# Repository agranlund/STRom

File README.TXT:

----------------------------------------------------------------------------
ROM board for Atari STM
(c)2020, Anders Granlund
----------------------------------------------------------------------------
Tested on a C070243 Rev.I motherboard, your mileage may vary.
----------------------------------------------------------------------------

This board does not perform TOS2.x decoding but it has provisions to hook
it up to an external decoder.

pin CEO is the original chip select output
pin CEI is chip select input from external decoder

Bridge the CEO/CEI pins if you're not using an external TOS decoder.

----------------------------------------------------------------------------
TOS select header
----------------------------------------------------------------------------
The leftmost pin header can be used to select TOS when using EEPROMs big
enough to fit multiple TOSs on them.

Upper two pins controls A18 and the lower two controls A19.
Jumper to pull the signal low.

For example:
39SF010 fits one TOS (A18+A19 are ignored)
39SF020 fits two TOS's (A18 is used to select, A19 is ignored)
39SF040 fits four TOS's (both A18 and A19 are used to select)

----------------------------------------------------------------------------
ROM size mode:
----------------------------------------------------------------------------
If your motherboard has the 256K/1M rom size jumpers and has already been
adjusted to work in 1M mode then you need only to bridge the three
solder jumpers on the rom board to the 1M position.

If the motherboard is in 256K mode, or if it lacks rom jumpers,
then you need to do the following:
- Bridge the three solder jumpers to the 256K position.
- Fit the 74LS11
- Fit the 100nF capacitor next to the 74LS11
- Solder wires from A16+A17 from the CPU to the A16+A17 headers
  on the rom board.

----------------------------------------------------------------------------
Realtime clock:
----------------------------------------------------------------------------
It takes a Dallas DS1315 chip and drivers can be found here:
https://github.com/agranlund/rtc

If you don't fit the DS1315 you need to bridge the "disable"
solder jumper.

----------------------------------------------------------------------------
BOM:
----------------------------------------------------------------------------
- Pin headers and sockets
- R1+R2: pullup resistors. The value is not terribly important, I used 3K3's

- Dallas DS1315 realtime clock
- 32.768Khz occilator for DS1315
- C1: 100nf capacitor for DS1315
- Battery holder for DS1315. I am using this one:
https://www.electrokit.com/en/product/battery-holder-cr2016-2025-2032-plastic/

- 74LS11N for motherboards in 256K mode
- C2: 100nf capacitor 74LS11N

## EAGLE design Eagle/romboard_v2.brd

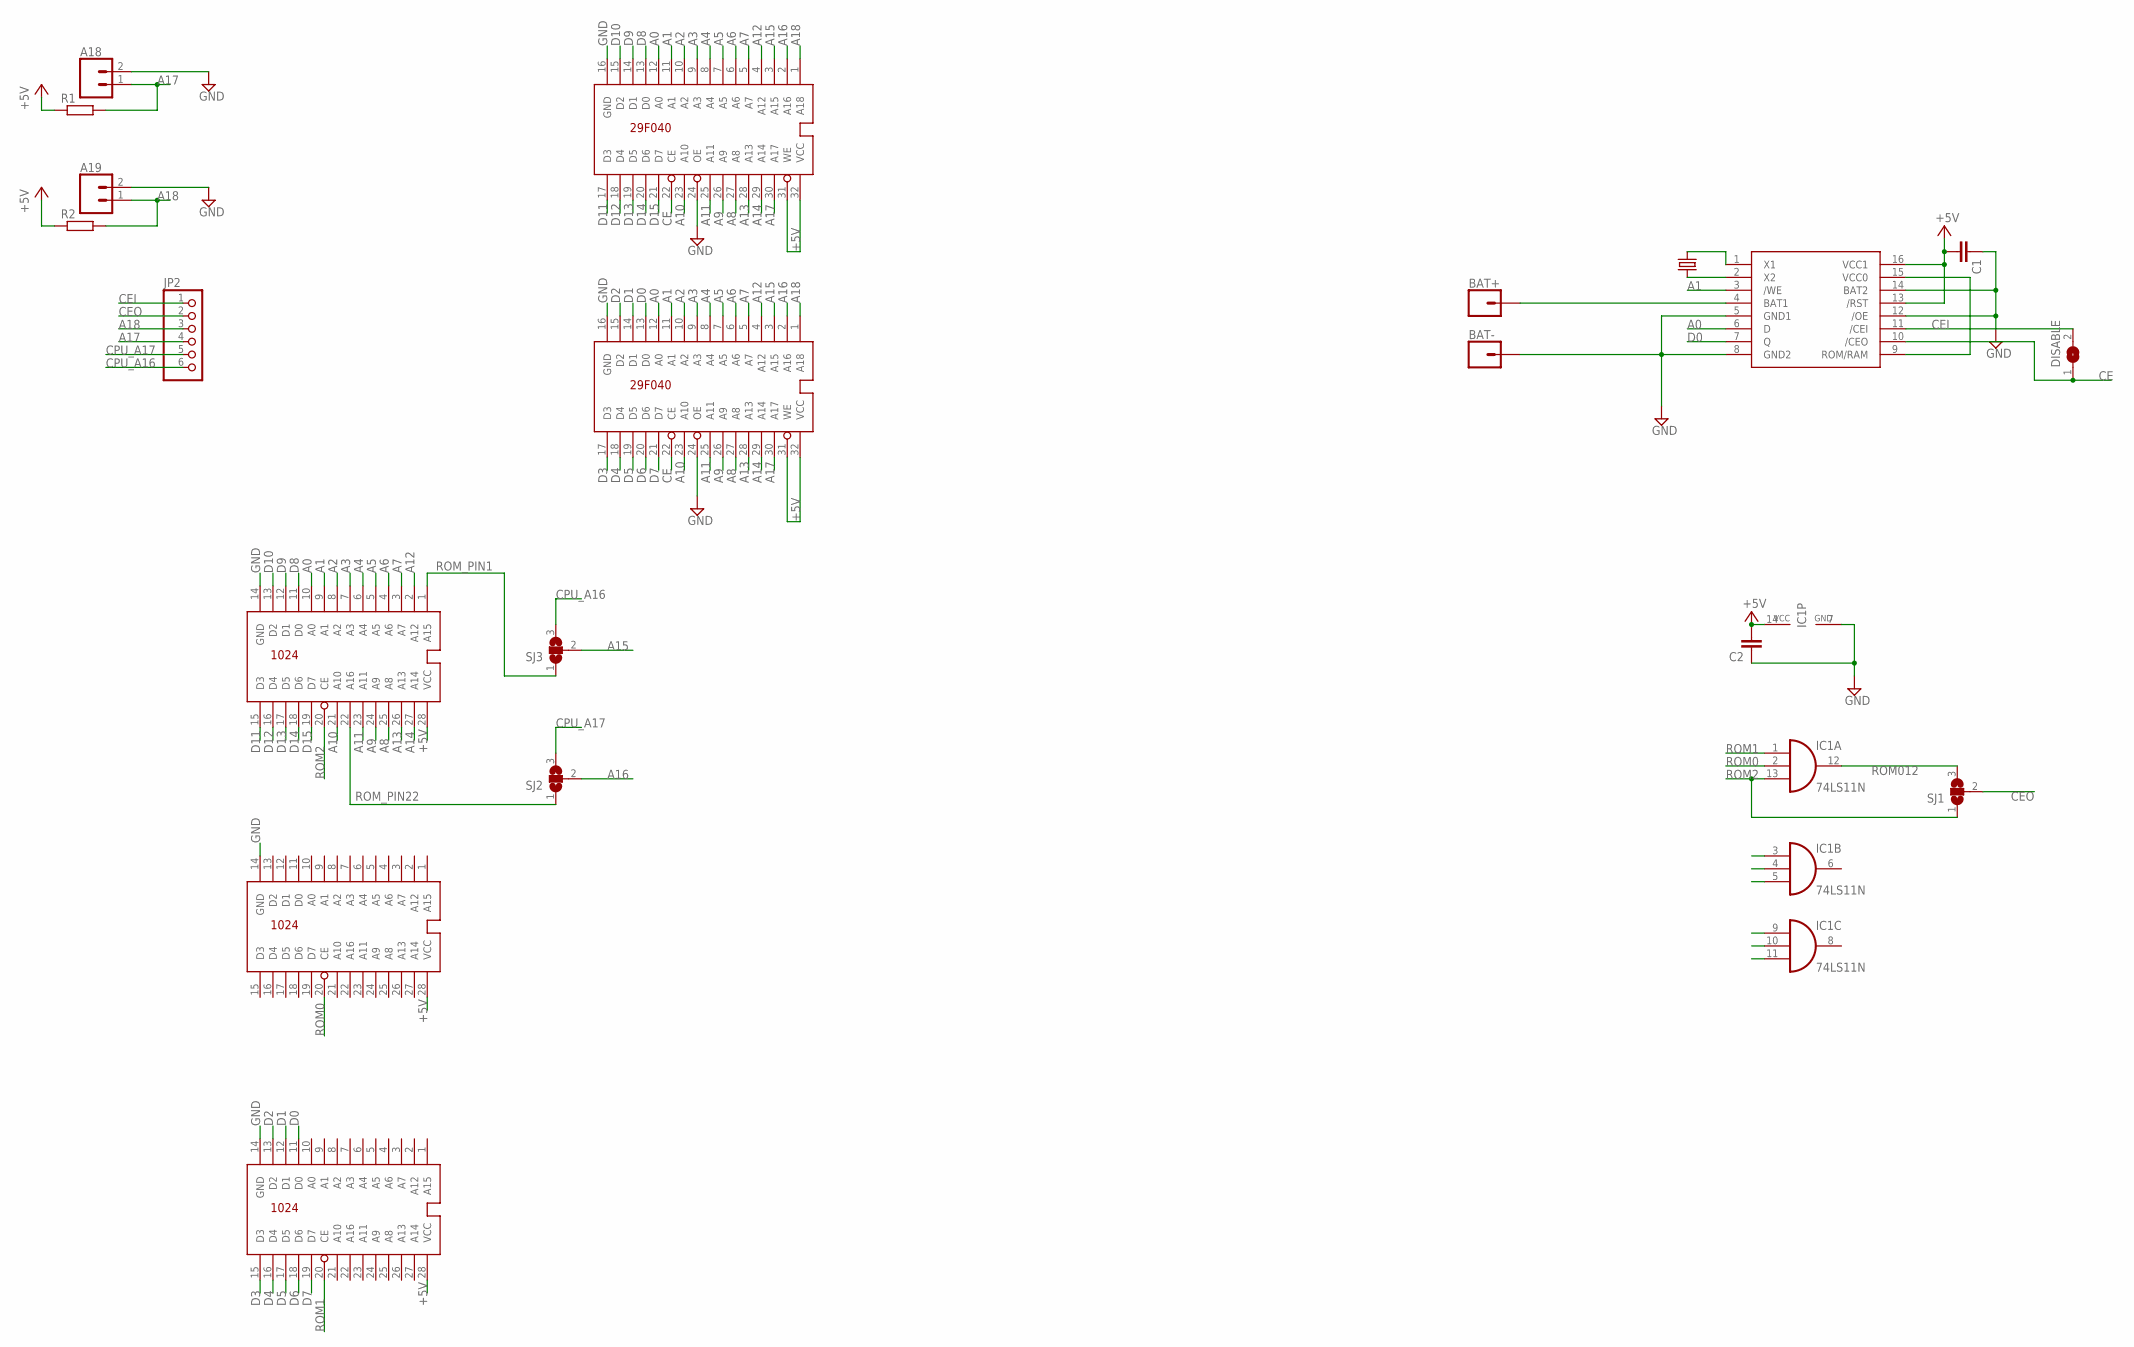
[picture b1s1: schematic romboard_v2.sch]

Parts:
32.768KHZ: CRYSTALTC38H; TC38H
A18, A19: CONN_02; 1X02
BAT+: CONN_01; 1X01
BAT-: CONN_01; 1X01
C1, C2: C-EU050-025X075; C050-025X075
DISABLE: SJ
HI0_SOCKET: ROM1024; ROM28PIN
IC1: 74LS11N; DIL14
JP2: PINHD-1X6/90; 1X06/90
LO2_SOCKET, LO2_SOCKET1: ROM1024; ROM28PIN
R1, R2: R-EU_0207/12; 0207/12
SJ1, SJ2, SJ3: SJ2W; SJ_2
U$1, U$2: AM29F040
U$4: DS1315; DIL16

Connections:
+5V: C1.2, C2.2, HI0_SOCKET.28 (VCC), IC1.14 (VCC), LO2_SOCKET.28 (VCC), LO2_SOCKET1.28 (VCC), R1.1, R2.1, U$1.31 (WE), U$1.32 (VCC), U$2.31 (WE), U$2.32 (VCC), U$4.13 (/RST), U$4.16 (VCC1)
A0: HI0_SOCKET.10 (A0), U$1.12 (A0), U$2.12 (A0), U$4.6 (D)
A1: HI0_SOCKET.9 (A1), U$1.11 (A1), U$2.11 (A1), U$4.3 (/WE)
A2: HI0_SOCKET.8 (A2), U$1.10 (A2), U$2.10 (A2)
A3: HI0_SOCKET.7 (A3), U$1.9 (A3), U$2.9 (A3)
A4: HI0_SOCKET.6 (A4), U$1.8 (A4), U$2.8 (A4)
A5: HI0_SOCKET.5 (A5), U$1.7 (A5), U$2.7 (A5)
A6: HI0_SOCKET.4 (A6), U$1.6 (A6), U$2.6 (A6)
A7: HI0_SOCKET.3 (A7), U$1.5 (A7), U$2.5 (A7)
A8: HI0_SOCKET.25 (A8), U$1.27 (A8), U$2.27 (A8)
A9: HI0_SOCKET.24 (A9), U$1.26 (A9), U$2.26 (A9)
A10: HI0_SOCKET.21 (A10), U$1.23 (A10), U$2.23 (A10)
A11: HI0_SOCKET.23 (A11), U$1.25 (A11), U$2.25 (A11)
A12: HI0_SOCKET.2 (A12), U$1.4 (A12), U$2.4 (A12)
A13: HI0_SOCKET.26 (A13), U$1.28 (A13), U$2.28 (A13)
A14: HI0_SOCKET.27 (A14), U$1.29 (A14), U$2.29 (A14)
A15: SJ3.2, U$1.3 (A15), U$2.3 (A15)
A16: SJ2.2, U$1.2 (A16), U$2.2 (A16)
A17: A18.1, JP2.4, R1.2, U$1.30 (A17), U$2.30 (A17)
A18: A19.1, JP2.3, R2.2, U$1.1 (A18), U$2.1 (A18)
BAT: BAT+.1, U$4.4 (BAT1)
CE: DISABLE.1, U$1.22 (CE), U$2.22 (CE), U$4.10 (/CEO)
CEI: DISABLE.2, JP2.1, U$4.11 (/CEI)
CEO: JP2.2, SJ1.2
CPU_A16: JP2.6, SJ3.3
CPU_A17: JP2.5, SJ2.3
D0: LO2_SOCKET.11 (D0), U$1.13 (D0), U$4.7 (Q)
D1: LO2_SOCKET.12 (D1), U$1.14 (D1)
D2: LO2_SOCKET.13 (D2), U$1.15 (D2)
D3: LO2_SOCKET.15 (D3), U$1.17 (D3)
D4: LO2_SOCKET.16 (D4), U$1.18 (D4)
D5: LO2_SOCKET.17 (D5), U$1.19 (D5)
D6: LO2_SOCKET.18 (D6), U$1.20 (D6)
D7: LO2_SOCKET.19 (D7), U$1.21 (D7)
D8: HI0_SOCKET.11 (D0), U$2.13 (D0)
D9: HI0_SOCKET.12 (D1), U$2.14 (D1)
D10: HI0_SOCKET.13 (D2), U$2.15 (D2)
D11: HI0_SOCKET.15 (D3), U$2.17 (D3)
D12: HI0_SOCKET.16 (D4), U$2.18 (D4)
D13: HI0_SOCKET.17 (D5), U$2.19 (D5)
D14: HI0_SOCKET.18 (D6), U$2.20 (D6)
D15: HI0_SOCKET.19 (D7), U$2.21 (D7)
GND: A18.2, A19.2, BAT-.1, C1.1, C2.1, HI0_SOCKET.14 (GND), IC1.7 (GND), LO2_SOCKET.14 (GND), LO2_SOCKET1.14 (GND), U$1.16 (GND), U$1.24 (OE), U$2.16 (GND), U$2.24 (OE), U$4.5 (GND1), U$4.8 (GND2), U$4.12 (/OE), U$4.14 (BAT2)
unnamed: U$4.9 (ROM/RAM), U$4.15 (VCC0)
ROM0: IC1.2 (I1), LO2_SOCKET1.20 (CE)
ROM1: IC1.1 (I0), LO2_SOCKET.20 (CE)
ROM2: HI0_SOCKET.20 (CE), IC1.13 (I2), SJ1.1
ROM012: IC1.12 (O), SJ1.3
ROM_PIN1: HI0_SOCKET.1 (A15), SJ3.1
ROM_PIN22: HI0_SOCKET.22 (A16), SJ2.1
X1: 32.768KHZ.2, U$4.1 (X1)
X2: 32.768KHZ.1, U$4.2 (X2)

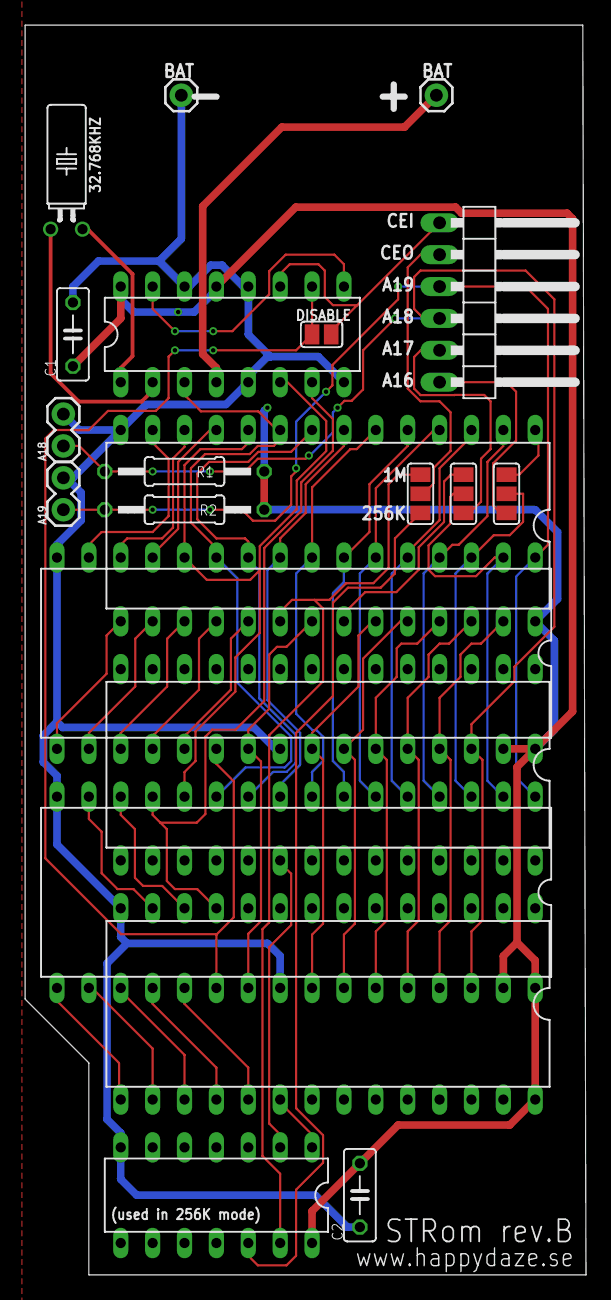
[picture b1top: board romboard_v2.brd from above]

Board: 2 copper layers, 44.7 x 99.6 mm, 21 parts (0 on the bottom side), 52 nets.

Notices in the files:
parts and their libraries:
SparkFun-Connectors: Licensing: Creative Commons ShareAlike 4.0 International - https://creativecommons.org/licenses/by-sa/4.0
